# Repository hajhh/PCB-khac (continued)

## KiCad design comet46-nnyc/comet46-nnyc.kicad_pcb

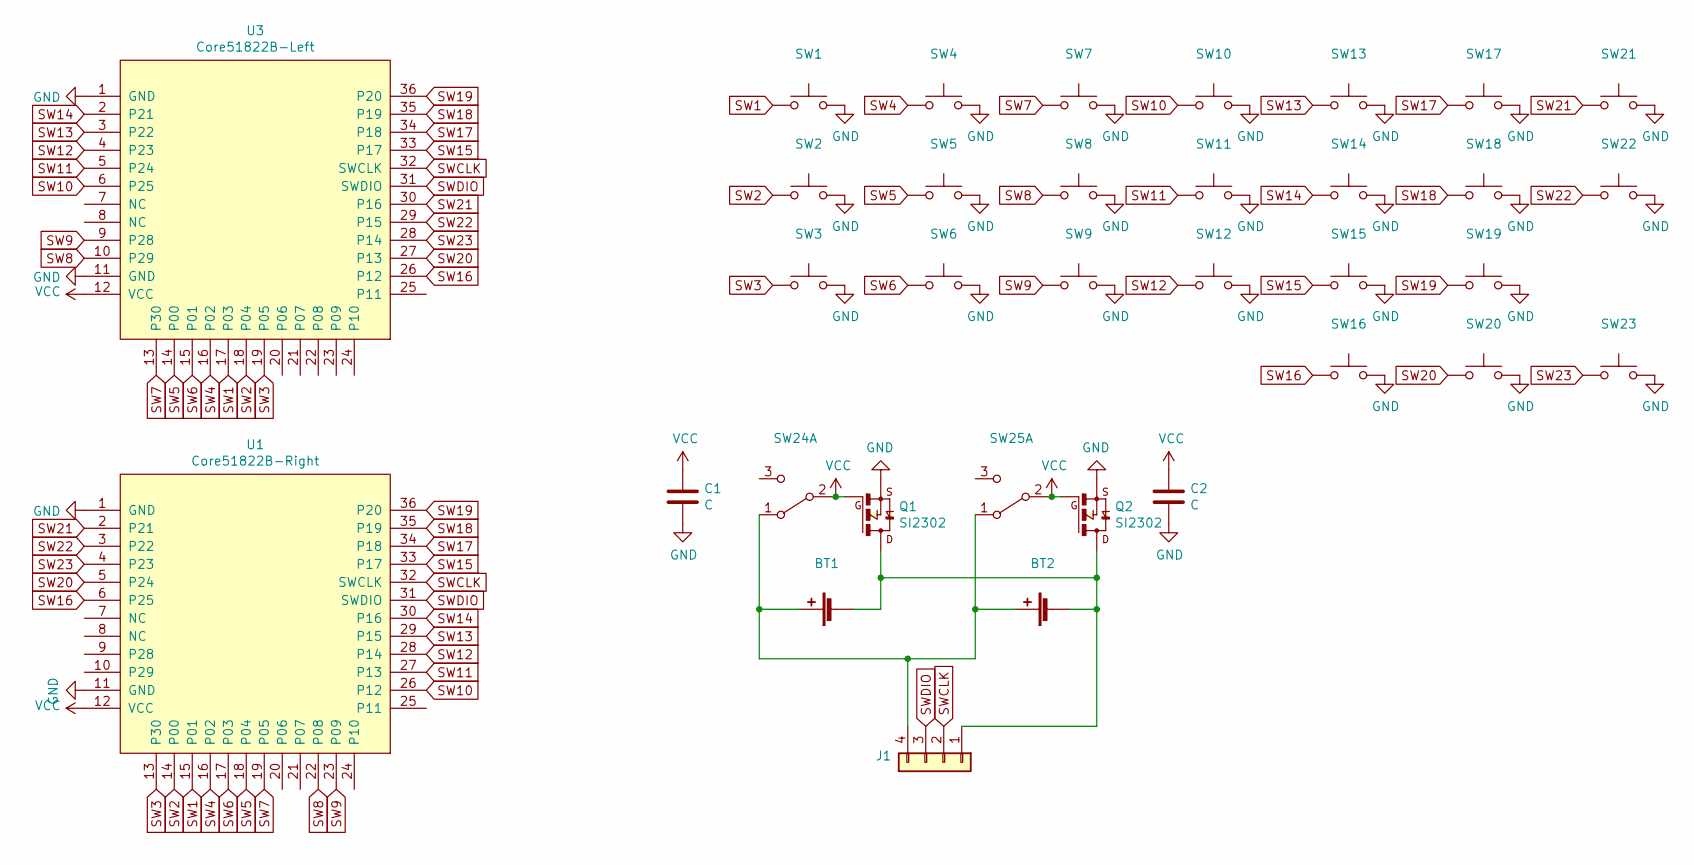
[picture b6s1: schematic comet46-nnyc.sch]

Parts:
BT1, BT2: BatteryHolder_Keystone_1060_1x2032
C1, C2: C; C_0603_1608Metric_Pad1.08x0.95mm_HandSolder
J1: PinHeader_1x04_P2.54mm_Horizontal
Q1, Q2: SI2302; SOT-23_Handsoldering
SW1, SW2, SW3, SW4, SW5, SW6, SW7, SW8, SW9, SW10, SW11, SW12, SW13, SW14, SW15, SW16, SW17, SW18, SW19, SW20, SW21, SW22, SW23: SW-1u-Aps-Split
SW24, SW25: SW_SPDT_PCM12
U1: Core51822B-Right; Core51822B
U3: Core51822B-Left; Core51822B

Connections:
GND: C1.2, C2.2, Q1.2, Q2.2, SW1.2, SW2.2, SW3.2, SW4.2, SW5.2, SW6.2, SW7.2, SW8.2, SW9.2, SW10.2, SW11.2, SW12.2, SW13.2, SW14.2, SW15.2, SW16.2, SW17.2, SW18.2, SW19.2, SW20.2, SW21.2, SW22.2, SW23.2, U1.1 (GND), U1.11 (GND), U3.1 (GND), U3.11 (GND)
unnamed: BT1.1 (+), BT2.1 (+), J1.4, SW24.1 (A), SW25.1 (A)
unnamed: BT1.2 (-), BT2.2 (-), J1.1, Q1.3, Q2.3
SW1: SW1.1, U1.15 (P01), U3.17 (P03)
SW2: SW2.1, U1.14 (P00), U3.18 (P04)
SW3: SW3.1, U1.13 (P30), U3.19 (P05)
SW4: SW4.1, U1.16 (P02), U3.16 (P02)
SW5: SW5.1, U1.18 (P04), U3.14 (P00)
SW6: SW6.1, U1.17 (P03), U3.15 (P01)
SW7: SW7.1, U1.19 (P05), U3.13 (P30)
SW8: SW8.1, U1.22 (P08), U3.10 (P29)
SW9: SW9.1, U1.23 (P09), U3.9 (P28)
SW10: SW10.1, U1.26 (P12), U3.6 (P25)
SW11: SW11.1, U1.27 (P13), U3.5 (P24)
SW12: SW12.1, U1.28 (P14), U3.4 (P23)
SW13: SW13.1, U1.29 (P15), U3.3 (P22)
SW14: SW14.1, U1.30 (P16), U3.2 (P21)
SW15: SW15.1, U1.33 (P17), U3.33 (P17)
SW16: SW16.1, U1.6 (P25), U3.26 (P12)
SW17: SW17.1, U1.34 (P18), U3.34 (P18)
SW18: SW18.1, U1.35 (P19), U3.35 (P19)
SW19: SW19.1, U1.36 (P20), U3.36 (P20)
SW20: SW20.1, U1.5 (P24), U3.27 (P13)
SW21: SW21.1, U1.2 (P21), U3.30 (P16)
SW22: SW22.1, U1.3 (P22), U3.29 (P15)
SW23: SW23.1, U1.4 (P23), U3.28 (P14)
SWCLK: J1.2, U1.32 (SWCLK), U3.32 (SWCLK)
SWDIO: J1.3, U1.31 (SWDIO), U3.31 (SWDIO)
VCC: C1.1, C2.1, Q1.1, Q2.1, SW24.2 (B), SW25.2 (B), U1.12 (VCC), U3.12 (VCC)

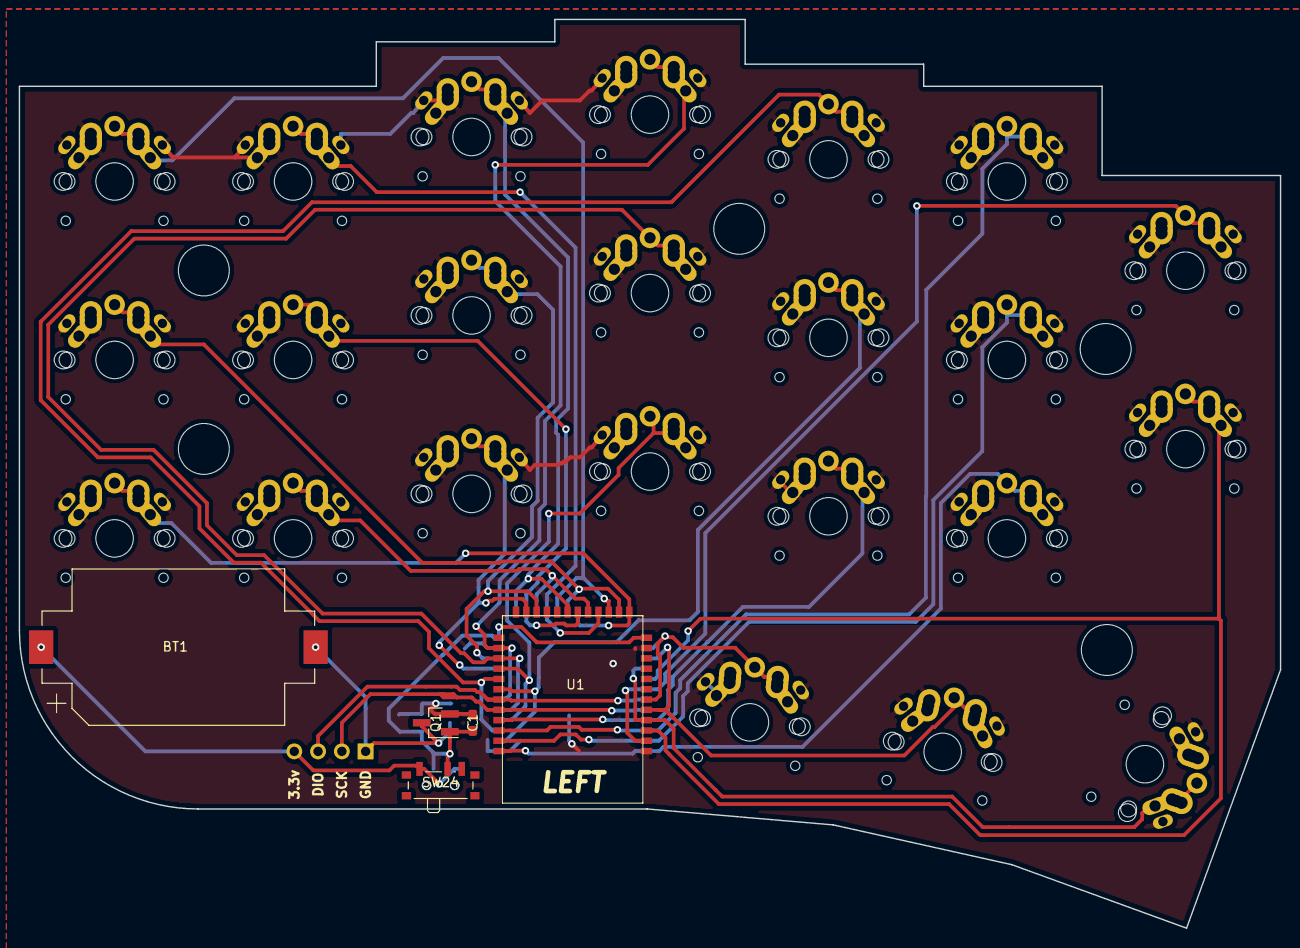
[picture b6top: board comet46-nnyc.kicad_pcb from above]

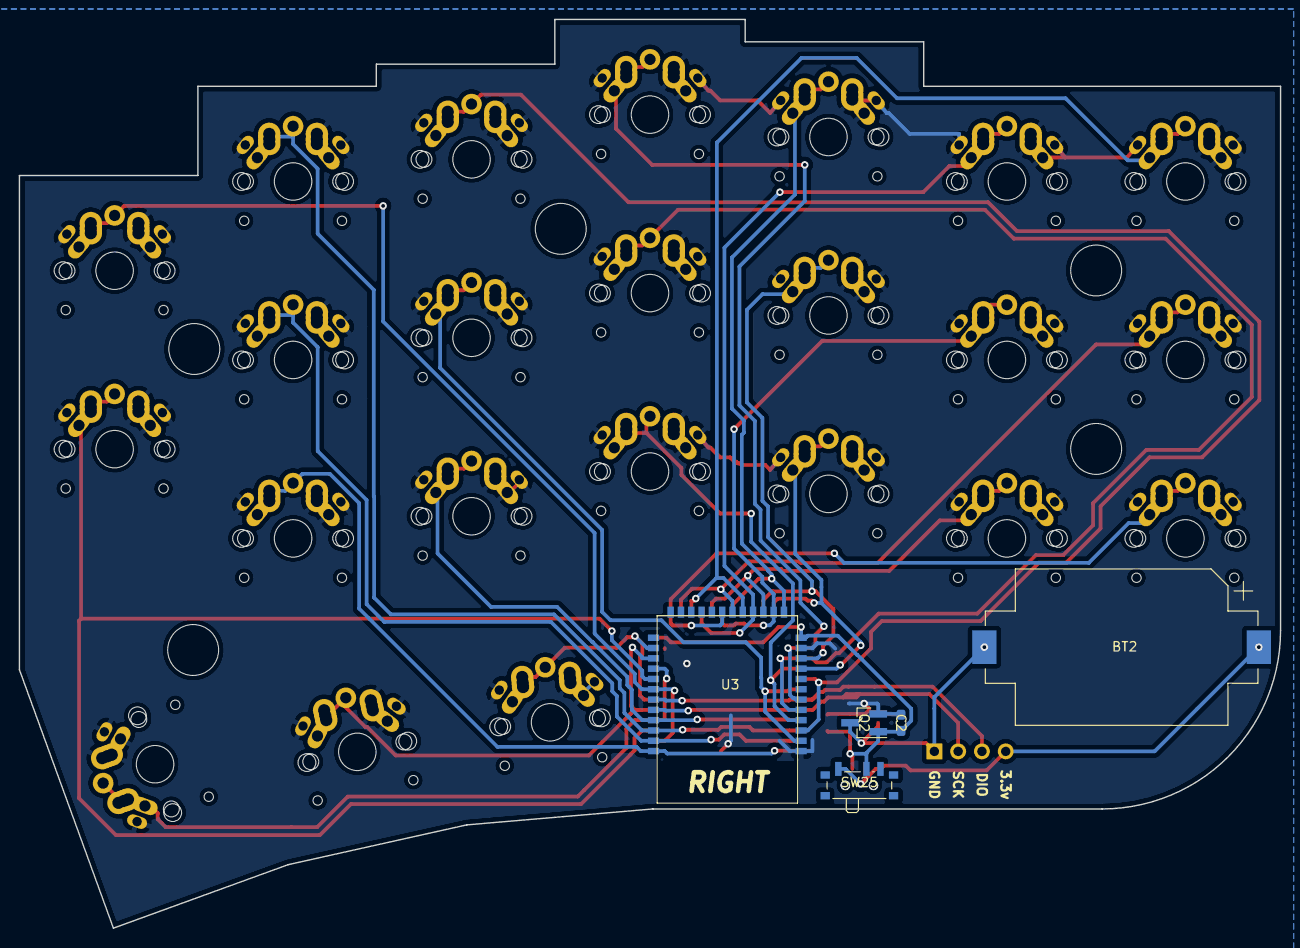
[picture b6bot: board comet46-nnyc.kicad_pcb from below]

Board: 2 copper layers, 134.6 x 97.0 mm, 34 parts (5 on the bottom side), 29 nets.

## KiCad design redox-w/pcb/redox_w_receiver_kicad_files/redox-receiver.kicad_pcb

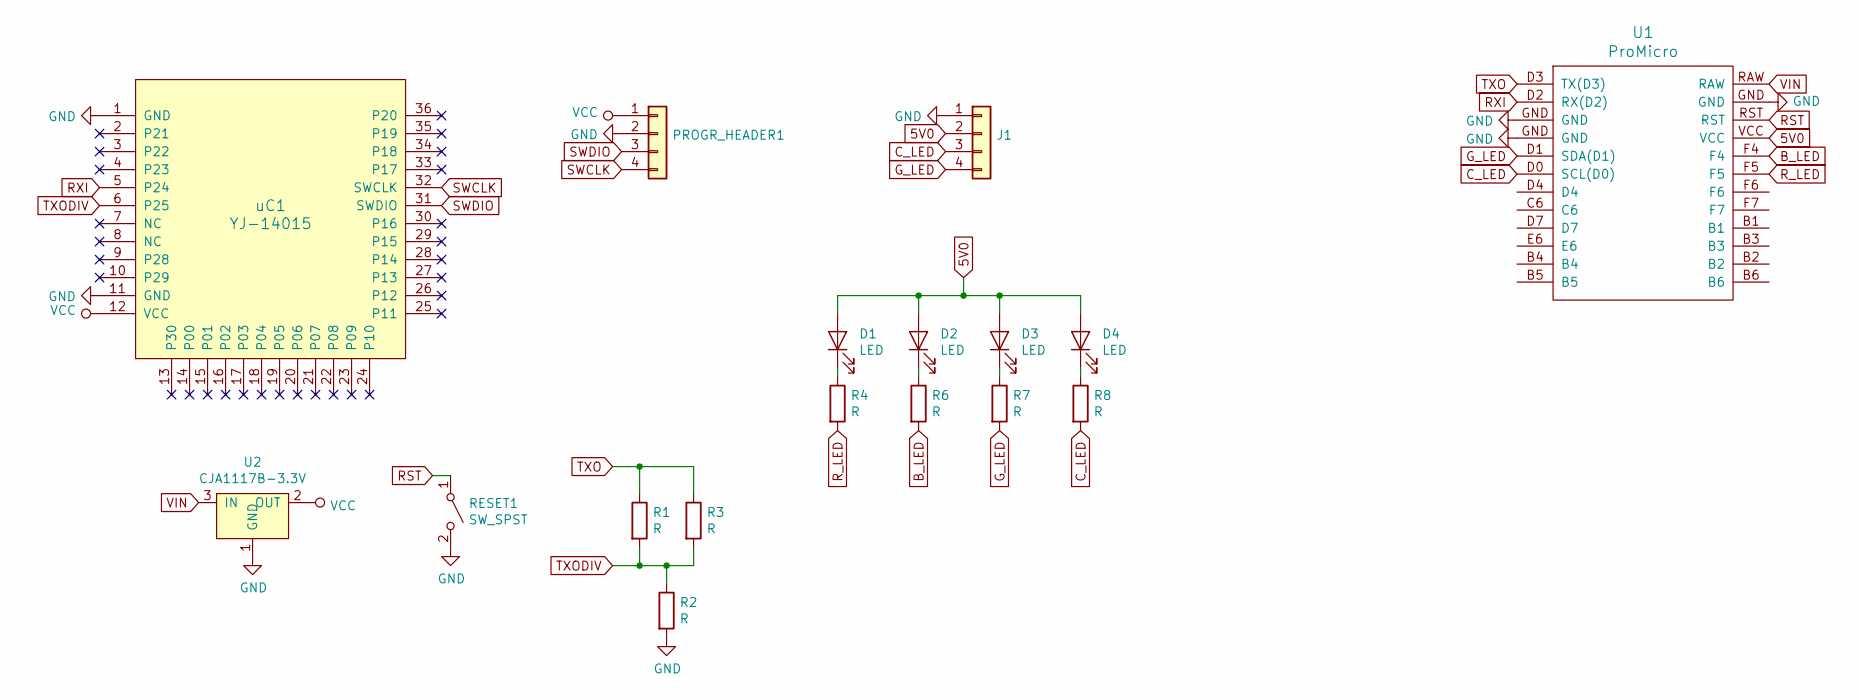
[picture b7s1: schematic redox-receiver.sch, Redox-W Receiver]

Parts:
D1, D2, D3, D4: LED; LED_0805_2012Metric_Pad1.15x1.40mm_HandSolder
J1: OLED_0.91'_FONTSIDE
PROGR_HEADER1: conn_04
R1, R2, R3, R4, R6, R7, R8: R; R_0805_2012Metric_Pad1.15x1.40mm_HandSolder
RESET1: SW_SPST; SW_SPST_CK_RS282G05A3
U1: ProMicro; pro micro
U2: CJA1117B-3.3V; SOT-89-3
uC1: YJ-14015; MY-YJ-14015-Module

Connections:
5V0: D1.2 (A), D2.2 (A), D3.2 (A), D4.2 (A), J1.2, U1.VCC
B_LED: R6.2, U1.F4
C_LED: J1.3, R8.2, U1.D0 (SCL(D0))
GND: J1.1, PROGR_HEADER1.2, R2.2, RESET1.2 (B), U1.GND, U2.1 (GND), uC1.1 (GND), uC1.11 (GND)
G_LED: J1.4, R7.2, U1.D1 (SDA(D1))
unnamed: D1.1 (K), R4.1
unnamed: D2.1 (K), R6.1
unnamed: D3.1 (K), R7.1
unnamed: D4.1 (K), R8.1
RST: RESET1.1 (A), U1.RST
RXI: U1.D2 (RX(D2)), uC1.5 (P24)
R_LED: R4.2, U1.F5
SWCLK: PROGR_HEADER1.4, uC1.32 (SWCLK)
SWDIO: PROGR_HEADER1.3, uC1.31 (SWDIO)
TXO: R1.1, R3.1, U1.D3 (TX(D3))
TXODIV: R1.2, R2.1, R3.2, uC1.6 (P25)
VCC: PROGR_HEADER1.1, U2.2 (OUT), uC1.12 (VCC)
VIN: U1.RAW, U2.3 (IN)

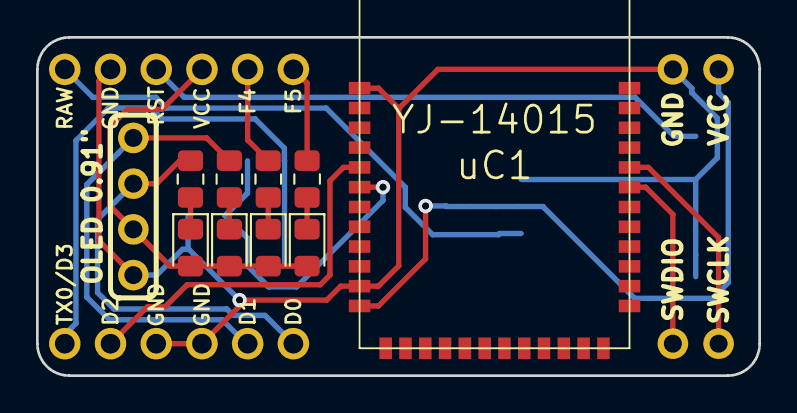
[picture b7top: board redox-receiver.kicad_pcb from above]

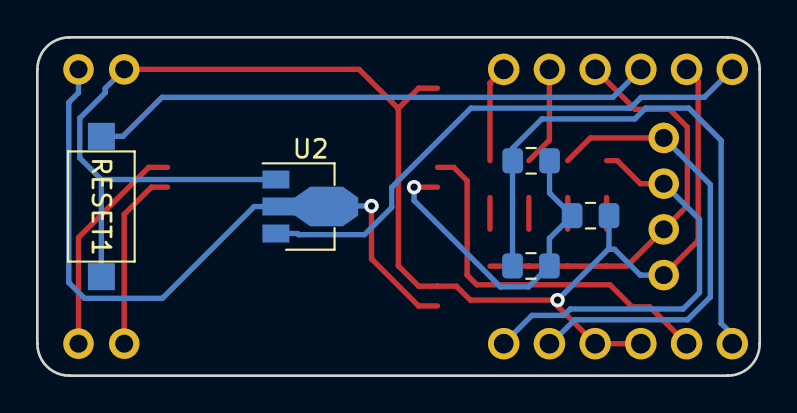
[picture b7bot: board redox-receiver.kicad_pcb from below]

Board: 2 copper layers, 40.1 x 18.8 mm, 17 parts (6 on the bottom side), 18 nets.

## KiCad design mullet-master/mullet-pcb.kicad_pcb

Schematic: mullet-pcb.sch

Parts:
C1: 1u; C_0603_1608Metric
C2, C3: 22p; C_0603_1608Metric
C4, C5, C6, C7, C9, C10, C11, C12, C13, C14, C15, C16, C17, C18, C19, C20, C21, C22: 0.1u; C_0603_1608Metric
C8: 4.7u; C_0603_1608Metric
D1, D2, D3, D4, D5, D6, D7, D8, D9, D10, D11, D12, D13, D14, D15, D16, D17, D18, D19, D20, D21, D22, D23, D24, D25, D26, D27, D28, D29, D30, D31, D32, D33, D34, D35, D36, D37, D38, D39, D40, D41, D42, D43, D44, D45, D46, D47, D48, D49, D50, D51, D52, D53, D54, D55, D56, D57, D58, D59, D60, D61, D62, D63, D64, D65, D66, D67: D_SOD-123
F1: 500mA; R_0805_2012Metric
ISCP1: Conn_02x03_Odd_Even; AVR_ICSP_3x2
LED1, LED2, LED3, LED4, LED5, LED6, LED7, LED8, LED9, LED10, LED11, LED12, LED13, LED14: WS2812B; LED_WS2812B_PLCC4_5.0x5.0mm_P3.2mm
R1, R2: 5.1k; R_0603_1608Metric
R3, R4: 10k; R_0603_1608Metric
R5, R6: 22; R_0603_1608Metric
RESET1: SW_SPST_TL3342
SW1, SW2, SW3, SW4, SW5, SW6, SW7, SW8, SW9, SW10, SW11, SW12, SW13, SW15, SW17, SW18, SW19, SW20, SW21, SW22, SW23, SW24, SW25, SW26, SW27, SW28, SW30, SW32, SW33, SW34, SW35, SW36, SW37, SW38, SW39, SW40, SW41, SW42, SW44, SW46, SW47, SW48, SW49, SW50, SW51, SW52, SW53, SW54, SW55, SW57, SW58, SW65, SW66, SW67: KEYSW; SW_Cherry_MX1A_1.00u_PCB-NOSCREEN
SW14: KEYSW; SW_Cherry_MX1A_2.00u_PCBNOSCREEN
SW16, SW29: KEYSW; SW_Cherry_MX1A_1.50u_PCBNOSCREEN
SW31, SW56: KEYSW; SW_Cherry_MX1A_1.75u_PCBNOSCREEN
SW43, SW45: KEYSW; SW_Cherry_MX1A_2.25u_PCBNOSCREEN
SW59, SW60, SW61, SW63, SW64: KEYSW; SW_Cherry_MX1A_1.25u_PCBNOSCREEN
SW62: KEYSW; SW_Cherry_MX_6.25u_PCB_ReversedStabilizer
U1: ATMEGA32U4; QFN-44-1EP_7x7mm_Pitch0.5mm
U2: PRTR5V0U2X; SOT143B
USB1: HRO-TYPE-C-31-M-12; HRO-TYPE-C-31-M-12-HandSoldering
X1: XTAL_GND; FA-238

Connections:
+5V: C4.1, C5.1, C6.1, C7.1, C8.1, C9.1, C10.1, C11.1, C12.1, C13.1, C14.1, C15.1, C16.1, C17.1, C18.1, C19.1, C20.1, C21.1, C22.1, F1.1, ISCP1.2, LED1.1, LED2.1, LED3.1, LED4.1, LED5.1, LED6.1, LED7.1, LED8.1, LED9.1, LED9.2, LED10.1, LED10.2, LED10.4, LED11.1, LED11.2, LED11.4, LED12.1, LED12.2, LED12.4, LED13.1, LED13.2, LED13.4, LED14.1, LED14.4, R3.2, U1.2 (UVcc), U1.7 (VBus), U1.14 (VCC), U1.24 (AVCC), U1.34 (VCC), U1.44 (AVCC)
D+: R6.2, U2.2 (IO1), USB1.6 (DP1), USB1.8 (DP2)
D-: R5.2, U2.3 (IO2), USB1.5 (DN2), USB1.7 (DN1)
unnamed: C1.1, U1.6 (UCap)
unnamed: C2.1, U1.16 (XTAL1), X1.1
unnamed: C3.1, U1.17 (XTAL2), X1.2
unnamed: D1.2, SW1.2
unnamed: D2.2, SW2.2
unnamed: D3.2, SW3.2
unnamed: D4.2, SW4.2
unnamed: D5.2, SW5.2
unnamed: D6.2, SW6.2
unnamed: D7.2, SW7.2
unnamed: D8.2, SW8.2
unnamed: D9.2, SW9.2
unnamed: D10.2, SW10.2
unnamed: D11.2, SW11.2
unnamed: D12.2, SW12.2
unnamed: D13.2, SW13.2
unnamed: D14.2, SW14.2
unnamed: D15.2, SW15.2
unnamed: D16.2, SW16.2
unnamed: D17.2, SW17.2
unnamed: D18.2, SW18.2
unnamed: D19.2, SW19.2
unnamed: D20.2, SW20.2
unnamed: D21.2, SW21.2
unnamed: D22.2, SW22.2
unnamed: D23.2, SW23.2
unnamed: D24.2, SW24.2
unnamed: D25.2, SW25.2
unnamed: D26.2, SW26.2
unnamed: D27.2, SW27.2
unnamed: D28.2, SW28.2
unnamed: D29.2, SW29.2
unnamed: D30.2, SW30.2
unnamed: D31.2, SW31.2
unnamed: D32.2, SW32.2
unnamed: D33.2, SW33.2
unnamed: D34.2, SW34.2
unnamed: D35.2, SW35.2
unnamed: D36.2, SW36.2
unnamed: D37.2, SW37.2
unnamed: D38.2, SW38.2
unnamed: D39.2, SW39.2
unnamed: D40.2, SW40.2
unnamed: D41.2, SW41.2
unnamed: D42.2, SW42.2
unnamed: D43.2, SW43.2
unnamed: D44.2, SW44.2
unnamed: D45.2, SW45.2
unnamed: D46.2, SW46.2
unnamed: D47.2, SW47.2
unnamed: D48.2, SW48.2
unnamed: D49.2, SW49.2
unnamed: D50.2, SW50.2
unnamed: D51.2, SW51.2
unnamed: D52.2, SW52.2
unnamed: D53.2, SW53.2
unnamed: D54.2, SW54.2
unnamed: D55.2, SW55.2
unnamed: D56.2, SW56.2
unnamed: D57.2, SW57.2
unnamed: D58.2, SW58.2
unnamed: D59.2, SW59.2
unnamed: D60.2, SW60.2
unnamed: D61.2, SW61.2
unnamed: D62.2, SW62.2
unnamed: D63.2, SW63.2
unnamed: D64.2, SW64.2
unnamed: D65.2, SW65.2
unnamed: D66.2, SW66.2
unnamed: D67.2, SW67.2
unnamed: LED1.2, LED2.4
unnamed: LED2.2, LED3.4
unnamed: LED3.2, LED4.4
unnamed: LED4.2, LED5.4
unnamed: LED5.2, LED6.4
unnamed: LED6.2, LED7.4
unnamed: LED7.2, LED8.4
unnamed: R1.2, USB1.4 (CC1)
unnamed: R2.2, USB1.10 (CC2)
unnamed: R4.2, U1.33 (~HWB/PE2)
unnamed: R5.1, U1.3 (D-)
unnamed: R6.1, U1.4 (D+)
RGB: LED1.4, U1.22 (PD5/XCK1)
VCC: F1.2, U2.4 (VCC), USB1.2 (VBUS), USB1.11 (VBUS)
col0: SW1.1, SW16.1, SW31.1, SW45.1, SW59.1, U1.10 (PB2/MOSI)
col1: SW2.1, SW17.1, SW32.1, SW60.1, U1.39 (PF4)
col2: ISCP1.3, SW3.1, SW18.1, SW33.1, SW46.1, SW61.1, U1.38 (PF5)
col3: ISCP1.4, SW4.1, SW19.1, SW34.1, SW47.1, U1.37 (PF6)
col4: ISCP1.1, SW5.1, SW20.1, SW35.1, SW48.1, U1.36 (PF7)
col5: SW6.1, SW21.1, SW36.1, SW49.1, U1.32 (PC7)
col6: SW7.1, SW22.1, SW37.1, SW50.1, SW62.1, U1.31 (PC6)
col7: SW8.1, SW23.1, SW38.1, SW51.1, U1.30 (PB6)
col8: SW9.1, SW24.1, SW39.1, SW52.1, U1.29 (PB5)
col9: SW10.1, SW25.1, SW40.1, SW53.1, U1.28 (PB4)
col10: SW11.1, SW26.1, SW41.1, SW54.1, SW63.1, U1.27 (T0/PD7)
col11: SW12.1, SW27.1, SW42.1, SW55.1, SW64.1, U1.26 (T1/PD6)
col12: SW13.1, SW28.1, SW56.1, SW65.1, U1.25 (ICP1/PD4)
col13: SW14.1, SW29.1, SW43.1, SW57.1, SW66.1, U1.20 (PD2/RXD1)
col14: SW15.1, SW30.1, SW44.1, SW58.1, SW67.1, U1.21 (PD3/TXD1)
led9din: LED8.2, LED9.4
reset: ISCP1.5, R3.1, RESET1.2, U1.13 (~RESET)
row0: D1.1, D2.1, D3.1, D4.1, D5.1, D6.1, D7.1, D8.1, D9.1, D10.1, D11.1, D12.1, D13.1, D14.1, D15.1, U1.18 (PD0/INT0)
row1: D16.1, D17.1, D18.1, D19.1, D20.1, D21.1, D22.1, D23.1, D24.1, D25.1, D26.1, D27.1, D28.1, D29.1, D30.1, U1.19 (PD1/INT1)
row2: D31.1, D32.1, D33.1, D34.1, D35.1, D36.1, D37.1, D38.1, D39.1, D40.1, D41.1, D42.1, D43.1, D44.1, U1.8 (PB0/SS)
row3: D45.1, D46.1, D47.1, D48.1, D49.1, D50.1, D51.1, D52.1, D53.1, D54.1, D55.1, D56.1, D57.1, D58.1, U1.41 (PF0)
row4: D59.1, D60.1, D61.1, D62.1, D63.1, D64.1, D65.1, D66.1, D67.1, U1.40 (PF1)

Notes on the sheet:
MULLET 65% keyboard with usb c and rgb underglow
2/24/2019
MULLET

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
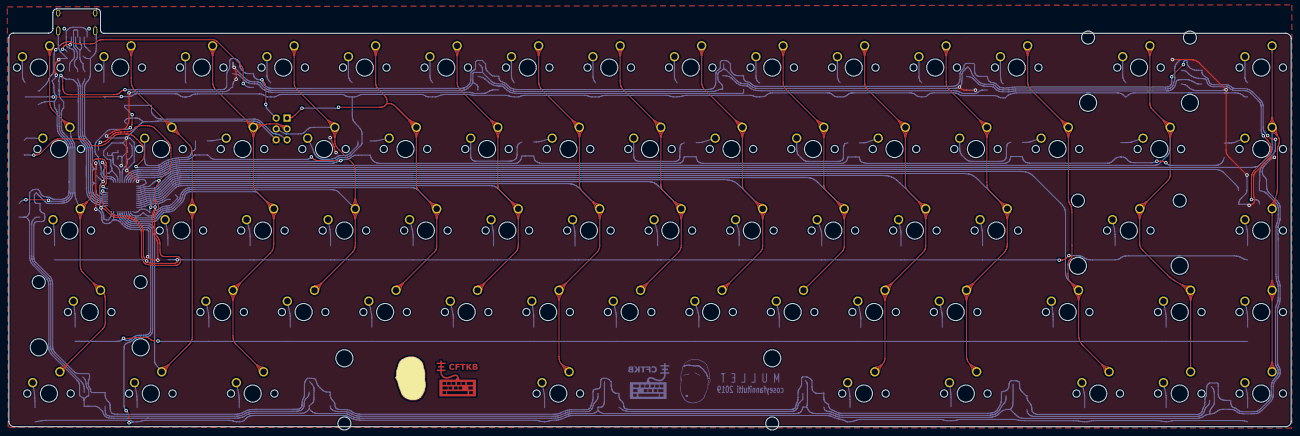
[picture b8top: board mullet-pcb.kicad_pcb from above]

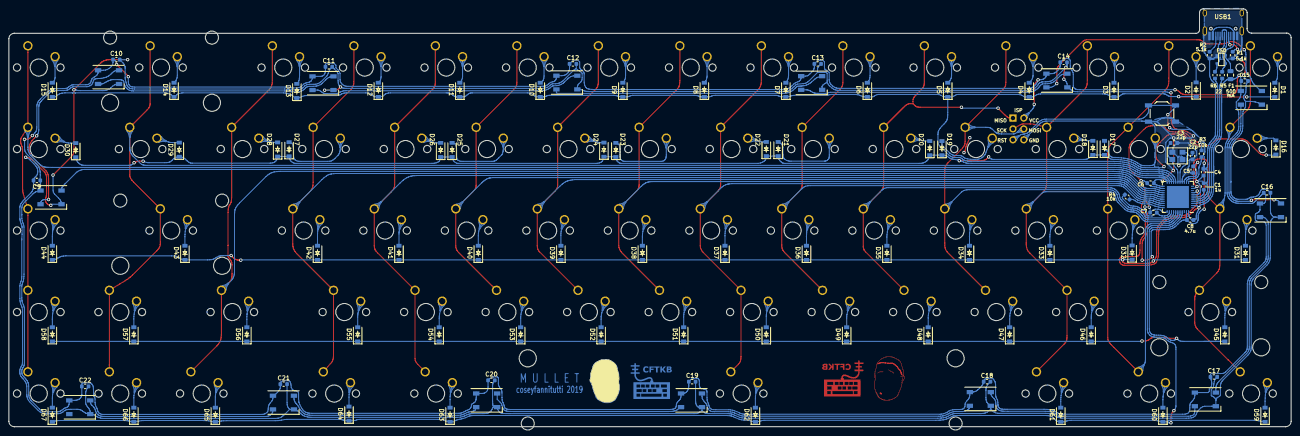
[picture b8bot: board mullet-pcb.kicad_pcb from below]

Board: 2 copper layers, 299.7 x 97.7 mm, 183 parts (116 on the bottom side), 110 nets.

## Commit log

2021-01-19 update PCB 20:42 19/01/2021
2021-01-19 update 00:43 20/01/2021
2021-01-19 update 00:44 20/01/2021
2021-01-24 update 13:33 24/01/2021
2021-01-28 update 17:18 28/01/2021
2021-01-30 add some keyboard
2021-01-30 update 21:14 29/01/2021 add some keyboard
2021-01-31 update 22:15 31/01/2021
2021-02-27 cap nhat 18:16 27/2/2021
2021-03-19 cap nhat 12:00 18/03/2021
